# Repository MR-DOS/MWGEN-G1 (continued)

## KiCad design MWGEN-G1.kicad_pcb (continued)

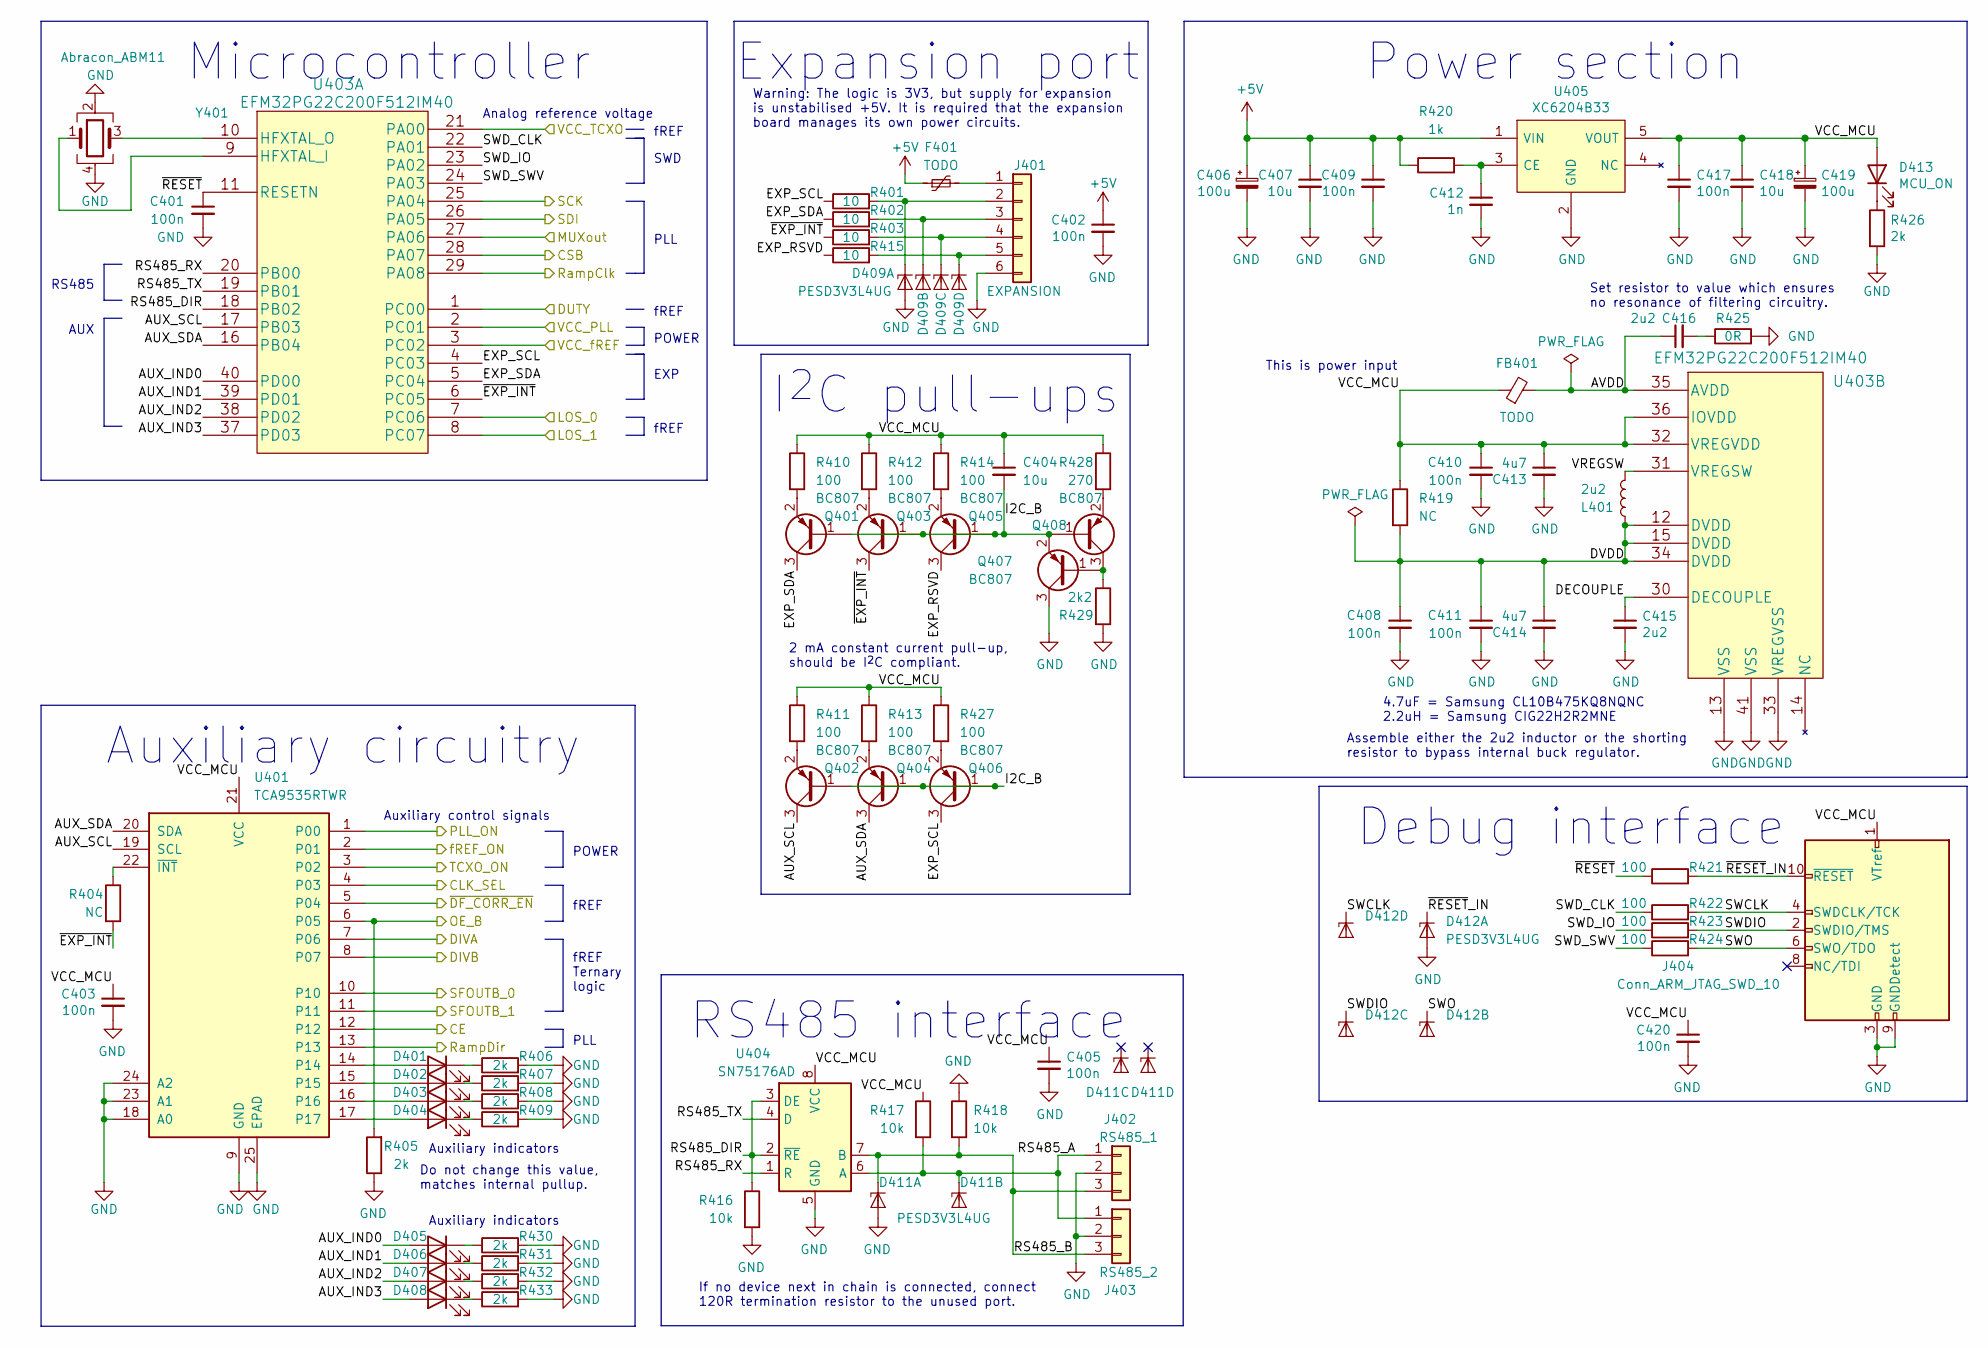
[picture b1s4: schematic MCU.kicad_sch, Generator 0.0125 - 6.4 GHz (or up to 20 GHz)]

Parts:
C401, C402, C403, C405, C408, C409, C410, C411, C417, C420: 100n; C_0603_1608Metric_Pad1.08x0.95mm_HandSolder
C404, C407, C418: 10u; C_0805_2012Metric_Pad1.18x1.45mm_HandSolder
C406, C419: 100u; CP_Elec_6.3x5.8
C412: 1n; C_0603_1608Metric_Pad1.08x0.95mm_HandSolder
C413, C414: 4u7; C_0603_1608Metric_Pad1.08x0.95mm_HandSolder
C415, C416: 2u2; C_0805_2012Metric_Pad1.18x1.45mm_HandSolder
D401, D402, D403, D404, D405, D406, D407, D408: LED_0603_1608Metric_Pad1.05x0.95mm_HandSolder
D409, D411, D412: PESD3V3L4UG; SOT-353_SC-70-5
D413: MCU_ON; LED_0603_1608Metric_Pad1.05x0.95mm_HandSolder
F401: TODO; Fuse_2920_7451Metric_Pad2.10x5.45mm_HandSolder
FB401: TODO; L_0603_1608Metric_Pad1.05x0.95mm_HandSolder
J401: EXPANSION; TE_84952-6_1x06-1MP_P1.0mm_Horizontal
J402: RS485_1; PhoenixContact_MSTBA_2,5_3-G-5,08_1x03_P5.08mm_Horizontal
J403: RS485_2; PhoenixContact_MSTBA_2,5_3-G-5,08_1x03_P5.08mm_Horizontal
J404: Conn_ARM_JTAG_SWD_10; ArmHeader_2x05-1_P1.27mm_Vertical_SMD_pin7removed
L401: 2u2; L_1008_2520Metric_Pad1.43x2.20mm_HandSolder
Q401, Q402, Q403, Q404, Q405, Q406, Q407, Q408: BC807; SOT-23
R401, R402, R403, R415: 10; R_0603_1608Metric_Pad0.98x0.95mm_HandSolder
R404, R419: NC; R_0603_1608Metric_Pad0.98x0.95mm_HandSolder
R405, R406, R407, R408, R409, R426, R430, R431, R432, R433: 2k; R_0603_1608Metric_Pad0.98x0.95mm_HandSolder
R410, R411, R412, R413, R414, R421, R422, R423, R424, R427: 100; R_0603_1608Metric_Pad0.98x0.95mm_HandSolder
R416, R417, R418: 10k; R_0603_1608Metric_Pad0.98x0.95mm_HandSolder
R420: 1k; R_0603_1608Metric_Pad0.98x0.95mm_HandSolder
R425: 0R; R_0603_1608Metric_Pad0.98x0.95mm_HandSolder
R428: 270; R_0603_1608Metric_Pad0.98x0.95mm_HandSolder
R429: 2k2; R_0603_1608Metric_Pad0.98x0.95mm_HandSolder
U401: TCA9535RTWR; WQFN-24-1EP_4x4mm_P0.5mm_EP2.45x2.45mm
U403: EFM32PG22C200F512IM40
U404: SN75176AD; SOIC-8_3.9x4.9mm_P1.27mm
U405: XC6204B33; SOT-89-5_Handsoldering
Y401: Abracon_ABM11; Crystal_SMD_Abracon_ABM3-4Pin_2.0x1.6mm

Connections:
+5V: C402.1, C406.1, C407.1, C409.1, F401.1, R420.1, U405.1 (VIN); also elsewhere on the board
/Clock reference/CLK_SEL: U401.4 (P03); also elsewhere on the board
/Clock reference/DIVA: U401.7 (P06); also elsewhere on the board
/Clock reference/DIVB: U401.8 (P07); also elsewhere on the board
/Clock reference/Input Clocks/DUTY_OUT_N: U403.1 (PC00); also elsewhere on the board
/Clock reference/OE_B: R405.2, U401.6 (P05); also elsewhere on the board
/Clock reference/SFOUTB_0: U401.10; also elsewhere on the board
/Clock reference/SFOUTB_1: U401.11; also elsewhere on the board
/Clock reference/TCXO_ON: U401.3 (P02); also elsewhere on the board
/Clock reference/fREF_ON: U401.2 (P01); also elsewhere on the board
/Clock reference/~DF_CORR_EN: U401.5 (P04); also elsewhere on the board
/LOS_EXT: U403.8 (PC07); also elsewhere on the board
/LOS_INT: U403.7 (PC06); also elsewhere on the board
/MCU/AUX_SCL: Q402.3 (C), U401.19 (SCL), U403.17 (PB03)
/MCU/AUX_SDA: Q404.3 (C), U401.20 (SDA), U403.16 (PB04)
/MCU/AVDD: C416.1, FB401.2, U403.35 (AVDD)
/MCU/CE: U401.12; also elsewhere on the board
/MCU/CSB: U403.28 (PA07); also elsewhere on the board
/MCU/DECOUPLE: C415.1, U403.30 (DECOUPLE)
/MCU/DVDD: C408.1, C411.1, C414.1, L401.2, R419.2, U403.12 (DVDD), U403.15 (DVDD), U403.34 (DVDD)
/MCU/EXP_RSVD: Q405.3 (C), R415.1
/MCU/EXP_SCL: Q406.3 (C), R401.1, U403.4 (PC03)
/MCU/EXP_SDA: Q401.3 (C), R402.1, U403.5 (PC04)
/MCU/I2C_B: C404.2, Q401.1 (B), Q402.1 (B), Q403.1 (B), Q404.1 (B), Q405.1 (B), Q406.1 (B), Q407.2 (E), Q408.1 (B)
/MCU/MUXout: U403.27 (PA06); also elsewhere on the board
/MCU/PLL_ON: U401.1 (P00); also elsewhere on the board
/MCU/RS485_A: D411.3 (K2), J402.1, J403.1, R417.2, U404.6 (A)
/MCU/RS485_B: D411.1 (K1), J402.3, J403.3, R418.2, U404.7 (B)
/MCU/RS485_DIR: R416.1, U403.18 (PB02), U404.2 (~RE), U404.3 (DE)
/MCU/RS485_RX: U403.20 (PB00), U404.1 (R)
/MCU/RS485_TX: U403.19 (PB01), U404.4 (D)
/MCU/RampClk: U403.29 (PA08); also elsewhere on the board
/MCU/RampDir: U401.13; also elsewhere on the board
/MCU/SCK: U403.25 (PA04); also elsewhere on the board
/MCU/SDI: U403.26 (PA05); also elsewhere on the board
/MCU/SWCLK: D412.5 (K4), J404.4 (SWDCLK/TCK), R422.2
/MCU/SWDIO: D412.4 (K3), J404.2 (SWDIO/TMS), R423.2
/MCU/SWD_CLK: R422.1, U403.22 (PA01)
/MCU/SWD_IO: R423.1, U403.23 (PA02)
/MCU/SWD_SWV: R424.1, U403.24 (PA03)
/MCU/SWO: D412.3 (K2), J404.6 (SWO/TDO), R424.2
/MCU/VCC_MCU: C403.1, C404.1, C405.1, C410.1, C413.1, C417.1, C418.1, C419.1, C420.1, D413.2 (A), FB401.1, J404.1 (VTref), R410.1, R411.1, R412.1, R413.1, R414.1, R417.1, R419.1, R427.1, R428.1, U401.21 (VCC), U403.32 (VREGVDD), U403.36 (IOVDD), U404.8 (VCC), U405.5 (VOUT)
/MCU/VCC_PLL: U403.2 (PC01); also elsewhere on the board
/MCU/VCC_TCXO: U403.21 (PA00); also elsewhere on the board
/MCU/VCC_fREF: U403.3 (PC02); also elsewhere on the board
/MCU/VREGSW: L401.1, U403.31 (VREGSW)
/MCU/~EXP_INT: Q403.3 (C), R403.1, R404.2, U403.6 (PC05)
/MCU/~RESET: C401.1, R421.1, U403.11 (RESETN)
/MCU/~RESET_IN: D412.1 (K1), J404.10 (~RESET), R421.2
GND: C401.2, C402.2, C403.2, C405.2, C406.2, C407.2, C408.2, C409.2, C410.2, C411.2, C412.2, C413.2, C414.2, C415.2, C417.2, C418.2, C419.2, C420.2, D409.2 (A), D411.2 (A), D412.2 (A), J401.6, J402.2, J403.2, J404.3 (GND), J404.5 (GND), J404.9 (GNDDetect), Q407.3 (C), R405.1, R406.2, R407.2, R408.2, R409.2, R416.2, R418.1, R425.2, R426.2, R429.2, R430.2, R431.2, R432.2, R433.2, U401.9 (GND), U401.18 (A0), U401.23 (A1), U401.24 (A2), U401.25 (EPAD), U403.13 (VSS), U403.33 (VREGVSS), U403.41 (VSS), U404.5 (GND), U405.2 (GND), Y401.2, Y401.4; also elsewhere on the board
unnamed: C412.1, R420.2, U405.3 (CE)
unnamed: C416.2, R425.1
unnamed: D401.1 (K), R406.1
unnamed: D401.2 (A), U401.14
unnamed: D402.1 (K), R407.1
unnamed: D402.2 (A), U401.15
unnamed: D403.1 (K), R408.1
unnamed: D403.2 (A), U401.16
unnamed: D404.1 (K), R409.1
unnamed: D404.2 (A), U401.17
unnamed: D405.1 (K), R430.1
unnamed: D406.1 (K), R431.1
unnamed: D407.1 (K), R432.1
unnamed: D408.1 (K), R433.1
unnamed: D409.1 (K1), J401.2, R401.2
unnamed: D409.3 (K2), J401.3, R402.2
unnamed: D409.4 (K3), J401.4, R403.2
unnamed: D409.5 (K4), J401.5, R415.2
unnamed: D413.1 (K), R426.1
unnamed: F401.2, J401.1
unnamed: Q401.2 (E), R410.2
unnamed: Q402.2 (E), R411.2
unnamed: Q403.2 (E), R412.2
unnamed: Q404.2 (E), R413.2
unnamed: Q405.2 (E), R414.2
unnamed: Q406.2 (E), R427.2
unnamed: Q407.1 (B), Q408.3 (C), R429.1
unnamed: Q408.2 (E), R428.2
unnamed: R404.1, U401.22 (~INT)
unnamed 207: D405.2 (A), U403.40 (PD00); also elsewhere on the board
unnamed 208: D406.2 (A), U403.39 (PD01); also elsewhere on the board
unnamed 209: D407.2 (A), U403.38 (PD02); also elsewhere on the board
unnamed 210: D408.2 (A), U403.37 (PD03); also elsewhere on the board
unnamed: U403.9 (HFXTAL_I), Y401.1
unnamed: U403.10 (HFXTAL_O), Y401.3

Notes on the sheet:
AUX
EXP
RS485
4.7uF = Samsung CL10B475KQ8NQNC 2.2uH = Samsung CIG22H2R2MNE
fREF
If no device next in chain is connected, connect 120R termination resistor to the unused port.
PLL
Set resistor to value which ensures no resonance of filtering circuitry.
SWD
POWER
Warning: The logic is 3V3, but supply for expansion is unstabilised +5V. It is required that the expansion board manages its own power circuits.
Analog reference voltage
Microcontroller
Auxiliary indicators
2 mA constant current pull-up, should be I^{2}C compliant.
I^{2}C pull-ups
fREF Ternary logic
Auxiliary circuitry
Expansion port
This is power input
Power section
Debug interface
RS485 interface
Auxiliary control signals
Assemble either the 2u2 inductor or the shorting resistor to bypass internal buck regulator.
Do not change this value, matches internal pullup.

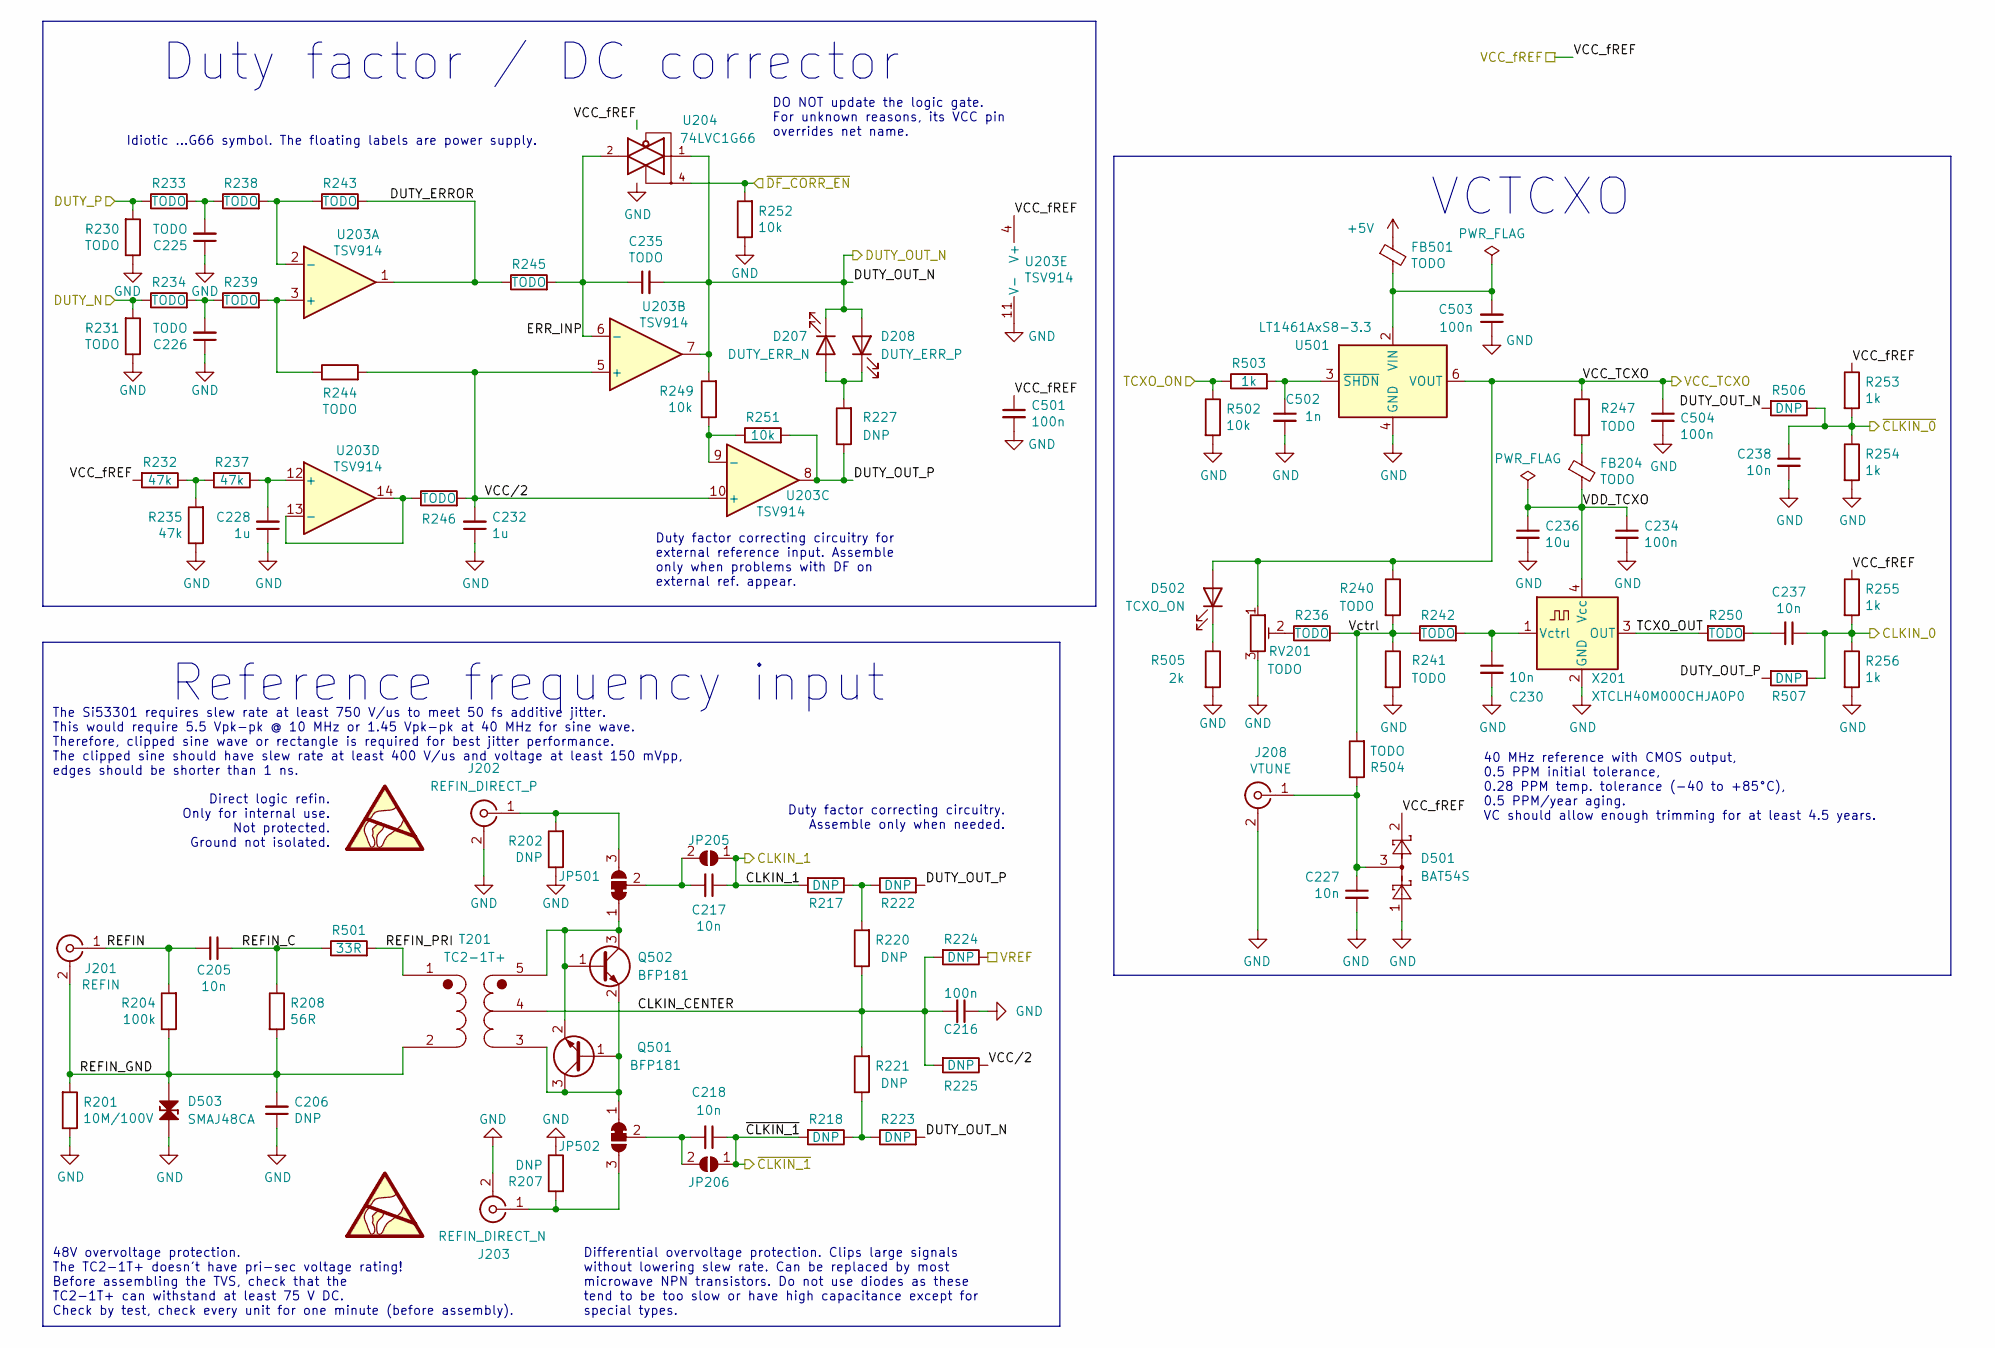
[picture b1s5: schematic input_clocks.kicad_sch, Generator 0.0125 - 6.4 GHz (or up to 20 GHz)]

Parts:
C205, C217, C218, C227, C230, C237, C238: 10n; C_0603_1608Metric_Pad1.08x0.95mm_HandSolder
C206: DNP; C_0603_1608Metric_Pad1.08x0.95mm_HandSolder
C216, C234, C501, C503, C504: 100n; C_0603_1608Metric_Pad1.08x0.95mm_HandSolder
C225, C226, C235: TODO; C_0603_1608Metric_Pad1.08x0.95mm_HandSolder
C228, C232: 1u; C_0603_1608Metric_Pad1.08x0.95mm_HandSolder
C236: 10u; C_0805_2012Metric_Pad1.18x1.45mm_HandSolder
C502: 1n; C_0603_1608Metric_Pad1.08x0.95mm_HandSolder
D207: DUTY_ERR_N; LED_0603_1608Metric_Pad1.05x0.95mm_HandSolder
D208: DUTY_ERR_P; LED_0603_1608Metric_Pad1.05x0.95mm_HandSolder
D501: BAT54S; SOT-23
D502: TCXO_ON; LED_0603_1608Metric_Pad1.05x0.95mm_HandSolder
D503: SMAJ48CA; D_SMA_TVS
FB204, FB501: TODO; L_0603_1608Metric_Pad1.05x0.95mm_HandSolder
J201: REFIN; SMA_rosenberger_hybrid
J202: REFIN_DIRECT_P; U.FL_Molex_MCRF_73412-0110_Vertical
J203: REFIN_DIRECT_N; U.FL_Molex_MCRF_73412-0110_Vertical
J208: VTUNE; U.FL_Molex_MCRF_73412-0110_Vertical
JP205, JP206: SolderJumper_2_Open; SolderJumper-2_P1.3mm_Open_RoundedPad1.0x1.5mm
JP501, JP502: SolderJumper_3_Bridged12; SolderJumper-3_P1.3mm_Bridged12_RoundedPad1.0x1.5mm_NumberL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
Q501, Q502: BFP181; SOT-23_Handsoldering
R201: 10M/100V; R_1206_3216Metric_Pad1.30x1.75mm_HandSolder
R202, R207, R217, R218, R220, R221, R222, R223, R224, R225, R227, R506, R507: DNP; R_0603_1608Metric_Pad0.98x0.95mm_HandSolder
R204: 100k; R_0603_1608Metric_Pad0.98x0.95mm_HandSolder
R208: 56R; R_0603_1608Metric_Pad0.98x0.95mm_HandSolder
R230, R231, R233, R234, R236, R238, R239, R240, R241, R242, R243, R244, R245, R246, R247, R250, R504: TODO; R_0603_1608Metric_Pad0.98x0.95mm_HandSolder
R232, R235, R237: 47k; R_0603_1608Metric_Pad0.98x0.95mm_HandSolder
R249, R251, R252, R502: 10k; R_0603_1608Metric_Pad0.98x0.95mm_HandSolder
R253, R254, R255, R256, R503: 1k; R_0603_1608Metric_Pad0.98x0.95mm_HandSolder
R501: 33R; R_0603_1608Metric_Pad0.98x0.95mm_HandSolder
R505: 2k; R_0603_1608Metric_Pad0.98x0.95mm_HandSolder
RV201: TODO; Potentiometer_Bourns_3296Y_Vertical
T201: TC2-1T+; Transformer_MiniCircuits_AT224-1A
U203: TSV914; SOIC-14_3.9x8.7mm_P1.27mm
U204: 74LVC1G66; SOT-353_SC-70-5_Handsoldering
U501: LT1461AxS8-3.3; SOIC-8_3.9x4.9mm_P1.27mm
X201: XTCLH40M000CHJA0P0; Oscillator_SMD_Fordahl_DFAS15-4Pin_5.0x3.2mm_HandSoldering

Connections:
+5V: FB501.1; also elsewhere on the board
/Clock reference/CLKIN_0: C237.1, R255.2, R256.1, R507.1; also elsewhere on the board
/Clock reference/CLKIN_1: C217.1, JP205.1 (A), R217.2; also elsewhere on the board
/Clock reference/DUTY_N: R231.2, R234.1; also elsewhere on the board
/Clock reference/DUTY_P: R230.2, R233.1; also elsewhere on the board
/Clock reference/Input Clocks/CLKIN_CENTER: C216.2, R220.1, R221.2, R224.2, R225.2, T201.4 (SC)
/Clock reference/Input Clocks/DUTY_ERROR: R243.2, R245.1, U203.1
/Clock reference/Input Clocks/DUTY_OUT_N: C235.2, D207.1 (K), D208.2 (A), R223.2, R249.2, R506.2, U203.7, U204.1; also elsewhere on the board
/Clock reference/Input Clocks/DUTY_OUT_P: R222.2, R227.1, R251.2, R507.2, U203.8
/Clock reference/Input Clocks/ERR_INP: C235.1, R245.2, U203.6 (-), U204.2
/Clock reference/Input Clocks/REFIN: C205.2, J201.1 (In), R204.2
/Clock reference/Input Clocks/REFIN_C: C205.1, R208.1, R501.1
/Clock reference/Input Clocks/REFIN_GND: C206.2, D503.1 (K), J201.2 (Ext), R201.2, R204.1, R208.2, T201.2 (AB)
/Clock reference/Input Clocks/REFIN_PRI: R501.2, T201.1 (AA)
/Clock reference/Input Clocks/TCXO_OUT: R250.2, X201.3 (OUT)
/Clock reference/Input Clocks/VCC/2: C232.2, R225.1, R244.2, R246.2, U203.5 (+), U203.10 (+)
/Clock reference/Input Clocks/VDD_TCXO: C234.1, C236.1, FB204.2, X201.4 (Vcc)
/Clock reference/Input Clocks/Vctrl: R236.2, R240.2, R241.1, R242.1, R504.2
/Clock reference/TCXO_ON: R502.1, R503.1; also elsewhere on the board
/Clock reference/VREF: R224.1; also elsewhere on the board
/Clock reference/~CLKIN_0: C238.1, R253.2, R254.1, R506.1; also elsewhere on the board
/Clock reference/~CLKIN_1: C218.1, JP206.1 (A), R218.2; also elsewhere on the board
/Clock reference/~DF_CORR_EN: R252.2, U204.4; also elsewhere on the board
/VCC_TCXO: C504.1, D502.2 (A), R240.1, R247.1, RV201.1, U501.6 (VOUT); also elsewhere on the board
GND: C206.1, C216.1, C225.1, C226.1, C227.2, C228.1, C230.2, C232.1, C234.2, C236.2, C238.2, C501.2, C502.2, C503.1, C504.2, D501.1, D503.2 (A), J202.2 (Ext), J203.2 (Ext), J208.2 (Ext), R201.1, R202.1, R207.1, R230.1, R231.1, R235.1, R241.2, R252.1, R254.2, R256.2, R502.2, R505.2, RV201.3, U203.11 (V-), U204.3 (GND), U501.4 (GND), X201.2 (GND); also elsewhere on the board
unnamed: C217.2, JP205.2 (B), JP501.2 (C)
unnamed: C218.2, JP206.2 (B), JP502.2 (C)
unnamed: C225.2, R233.2, R238.1
unnamed: C226.2, R234.2, R239.1
unnamed: C227.1, D501.3, J208.1 (In), R504.1
unnamed: C228.2, R237.1, U203.12 (+)
unnamed: C230.1, R242.2, X201.1 (Vctrl)
unnamed: C237.2, R250.1
unnamed: C502.1, R503.2, U501.3 (~SHDN)
unnamed: C503.2, FB501.2, U501.2 (VIN)
unnamed: D207.2 (A), D208.1 (K), R227.2
unnamed: D502.1 (K), R505.1
unnamed: FB204.1, R247.2
unnamed: J202.1 (In), JP501.3 (B), R202.2
unnamed: J203.1 (In), JP502.3 (B), R207.2
unnamed: JP501.1 (A), Q501.2 (E), Q502.1 (B), Q502.3 (C), T201.5 (SB)
unnamed: JP502.1 (A), Q501.1 (B), Q501.3 (C), Q502.2 (E), T201.3 (SA)
unnamed: R217.1, R220.2, R222.1
unnamed: R218.1, R221.1, R223.1
unnamed: R232.1, R235.2, R237.2
unnamed: R236.1, RV201.2
unnamed: R238.2, R243.1, U203.2 (-)
unnamed: R239.2, R244.1, U203.3 (+)
unnamed: R246.1, U203.13 (-), U203.14
unnamed: R249.1, R251.1, U203.9 (-)
VCC_fREF: C501.1, D501.2, R232.2, R253.1, R255.1, U203.4 (V+), U204.5 (VCC_fREF); also elsewhere on the board

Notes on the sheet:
48V overvoltage protection. The TC2-1T+ doesn't have pri-sec voltage rating! Before assembling the TVS, check that the TC2-1T+ can withstand at least 75 V DC. Check by test, check every unit for one minute (before assembly).
40 MHz reference with CMOS output, 0.5 PPM initial tolerance, 0.28 PPM temp. tolerance (-40 to +85°C), 0.5 PPM/year aging. VC should allow enough trimming for at least 4.5 years.
DO NOT update the logic gate. For unknown reasons, its VCC pin overrides net name.
Differential overvoltage protection. Clips large signals without lowering slew rate. Can be replaced by most microwave NPN transistors. Do not use diodes as these tend to be too slow or have high capacitance except for special types.
VCTCXO
Duty factor / DC corrector
Reference frequency input
Duty factor correcting circuitry for external reference input. Assemble only when problems with DF on external ref. appear.
Idiotic ...G66 symbol. The floating labels are power supply.
Duty factor correcting circuitry. Assemble only when needed.
Direct logic refin. Only for internal use. Not protected. Ground not isolated.
The Si53301 requires slew rate at least 750 V/us to meet 50 fs additive jitter. This would require 5.5 Vpk-pk @ 10 MHz or 1.45 Vpk-pk at 40 MHz for sine wave. Therefore, clipped sine wave or rectangle is required for best jitter performance. The clipped sine should have slew rate at least 400 V/us 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

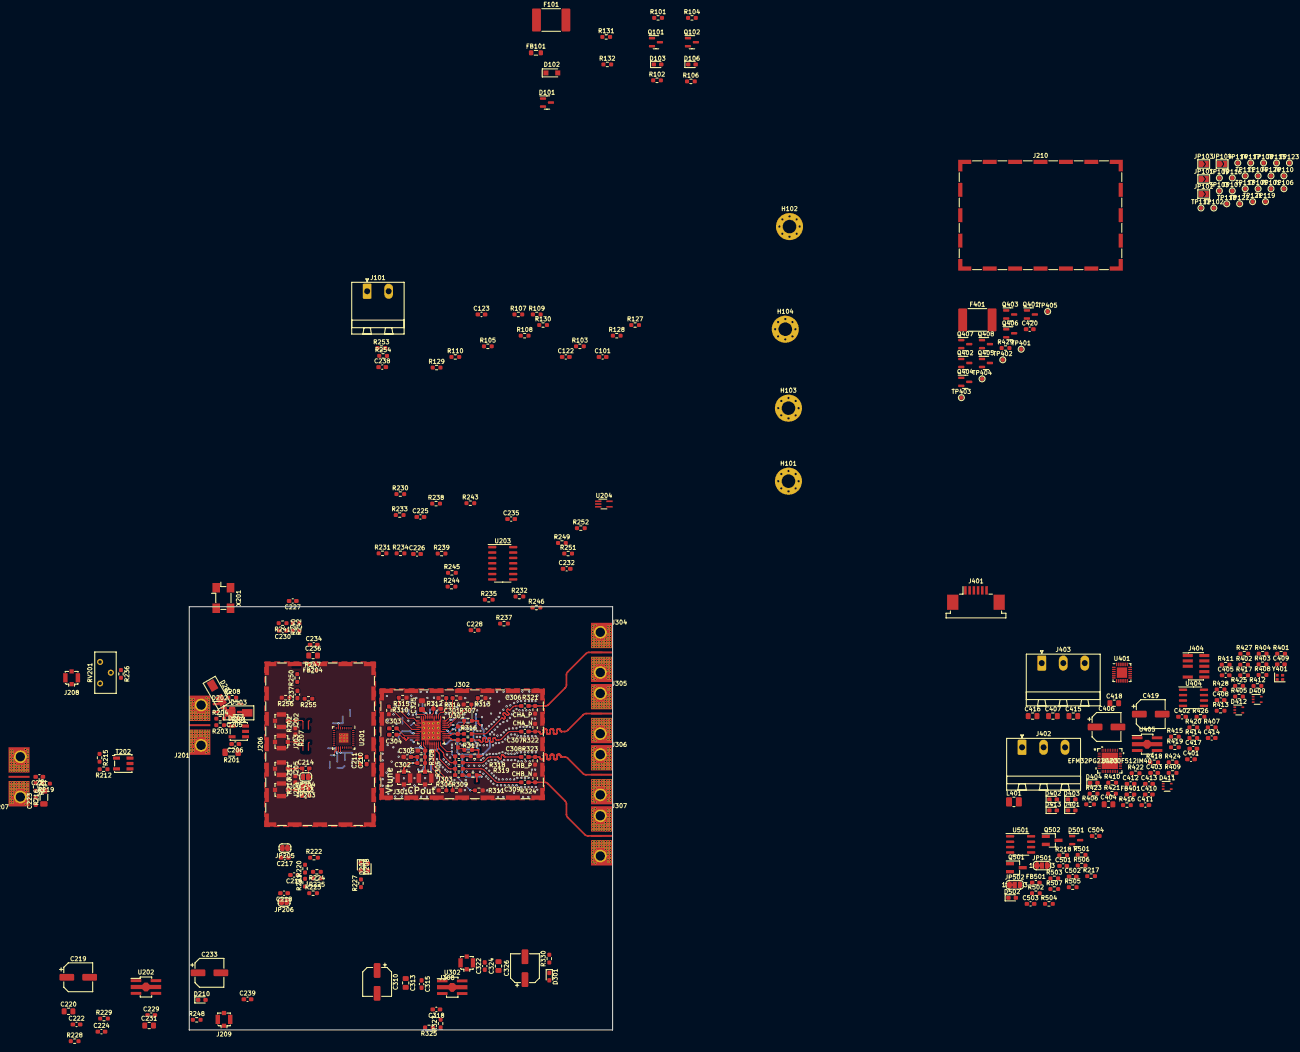
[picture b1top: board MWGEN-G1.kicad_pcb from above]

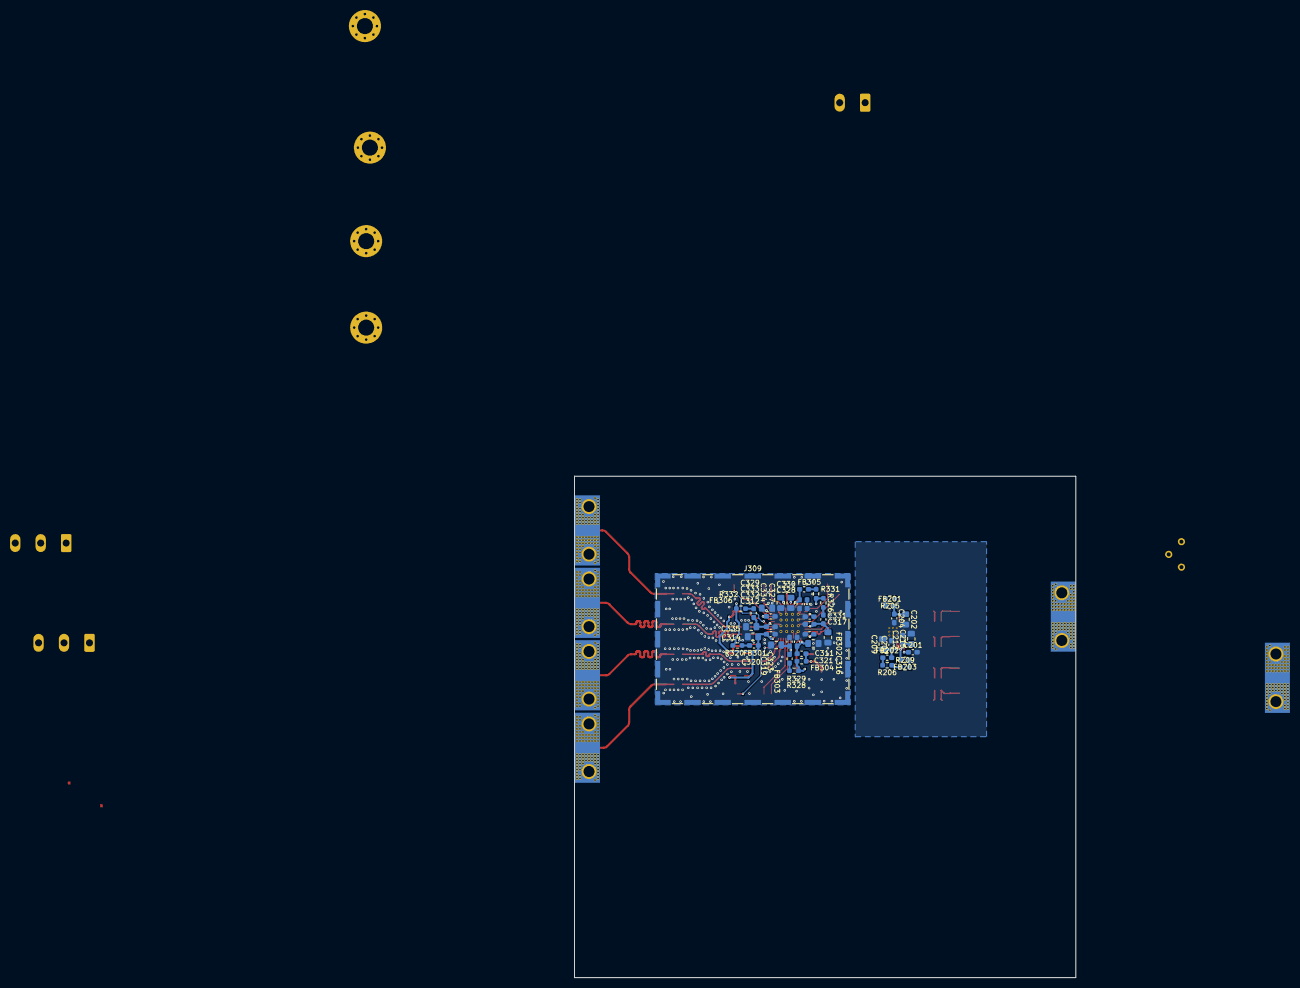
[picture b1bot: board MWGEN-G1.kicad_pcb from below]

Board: 4 copper layers, 100.0 x 100.0 mm, 373 parts (44 on the bottom side), 210 nets.

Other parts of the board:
TP401, TP402, TP403, TP404, TP405: TestPoint_Small; TestPoint_Pad_D1.0mm

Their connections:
GND: TP401.1; also elsewhere on the board
unnamed 207: TP402.1; also elsewhere on the board
unnamed 208: TP403.1; also elsewhere on the board
unnamed 209: TP404.1; also elsewhere on the board
unnamed 210: TP405.1; also elsewhere on the board

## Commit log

2021-02-25 Initial commit, schematic done, footprints matched, grouping on PCB in progress.
2021-02-25 Removed amplifier part which does not belong to this project, added symbol library.
2021-02-25 Added schemtic printout in PDF
2021-11-02 Working on making the original module a self-contained module with MCU. Added PCB.
2021-11-12 Updates to schematic
2021-11-12 Updated schematics
2021-11-13 Finished schematics
2021-11-13 Schematic fixes
2021-11-13 updated PDF
2021-11-14 Schematic checked. All footprints assigned. Electrolytics need footprint check, so do the RS485 and power connectors and the MuRata oscillator (also it is now EOL) and the crystal. The power protecti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
2021-11-23 Create LICENSE
    Added GPLv3 license
2021-12-08 Resolved all broken symbols / packages / links except TCXO.
2021-12-15 Footprint changes
2021-12-15 updated PDF with schematic
2021-12-29 Partially reworked aux interface, about to be remade once again.
2021-12-29 Remade and simplified AUX/EXT section.
2021-12-29 Updated schematics, remade AUX/EXT sections.
2021-12-29 Fixes.
2021-12-29 Plotted schematic
2021-12-30 Schematic ready for impoting changes into PCB.
2021-12-30 Synchronised PCB and schematic.
2021-12-30 Some minor fixes
2022-01-01 Minor improvements and fixes to schematic, added high current LDO needed for high frequency PLLs.
